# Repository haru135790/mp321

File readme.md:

# mp321-mpみつい

## 概要
mp321は、コンパクトな左手デバイスです。名刺サイズの基板に６つのキーとロータリーエンコーダーが搭載されています。
vialを使用してキー割り当てを自由に変更できます。

## 準備物
- mp321本体
- USBケーブル(AtoCまたはCtoC)
注意点：USBケーブルは通信ができるものを使用してください。100均等で「充電専用」として販売されているものは使用出来ません。

## キー割り当ての変更
本機のキー割り当ては「[vial](https://get.vial.today)」というソフトウェアを使用することで変更できます。
vialにはwebブラウザ版とアプリケーション版があり、ブラウザ版はChrome、アプリ版はWindows,macOS,Linuxで動作します。
また、2025/10/21時点で、vialは日本語対応していません。ご注意ください。

ここでは、vialを使用するとできることについて簡単に説明します。(詳細な操作方法等についてはネットで検索するか、後述の参考記事をご覧ください)
1. キーマップの変更
   - キーに割り当てられた機能を自由に変更できます。
   - キーボードに実際にあるキーだけでなく、メディアキー(音楽の再生/停止など)や、特殊キー(画面の明るさ調整など)も割り当て可能です。
   - 複数のキーを同時に押すショートカット(例: Ctrl+C)も一つのキーに割り当てられます。
2. マクロの設定
   - 複数のキー操作を一つのキーにまとめて割り当てることができます。
   - 例えば、「Ctrl+Aで全選択したあとに、Ctrl+Cでコピーする」といった連続した動作を一つのキーに設定することが可能です。
   - テキストの入力(「Hello, World!」と入力するなど)もマクロに含めることができます。
3. レイヤー機能
   - 複数のキーマップを作成し、特定のキーを押すことでキーマップを切り替えることができます。
   - 例えば、通常のキーマップと、ゲーム用のキーマップを切り替えることが可能です。
4. コンボキー
   - 複数のキーを同時に押すことで、別の機能を発動させることができます。
   - 例えば、AキーとBキーを同時に押すとCキーの機能が発動するように設定できます。
5. タップダンス
   - キーの押し方(単押し、長押し、単押し2回、単押しした直後に長押し)によって、異なる機能を割り当てることができます。
   - 例えば、普通にAキーを押すとAキーの機能が発動し、長押しするとBキーの機能が発動するように設定できます。

## 参考記事
vialの詳細な使用方法については、こちらの記事がおすすめです。
- [【初心者向け】Vialでキーボードをカスタムしよう！](https://alektor.hatenablog.com/entry/2024/11/15/233435)
- [（初心者編）Vialを使ってキーマップを書き換えよう-自作キーボード温泉街の歩き方](https://salicylic-acid3.hatenablog.com/entry/vial-manual)

## デフォルトキーマップ
mp321は初期状態では次のようなキー設定となっています。

mp321についているノブ(ロータリーエンコーダー)は、vial上では右回転と左回転、押し込みがそれぞれ分かれて表示されています。

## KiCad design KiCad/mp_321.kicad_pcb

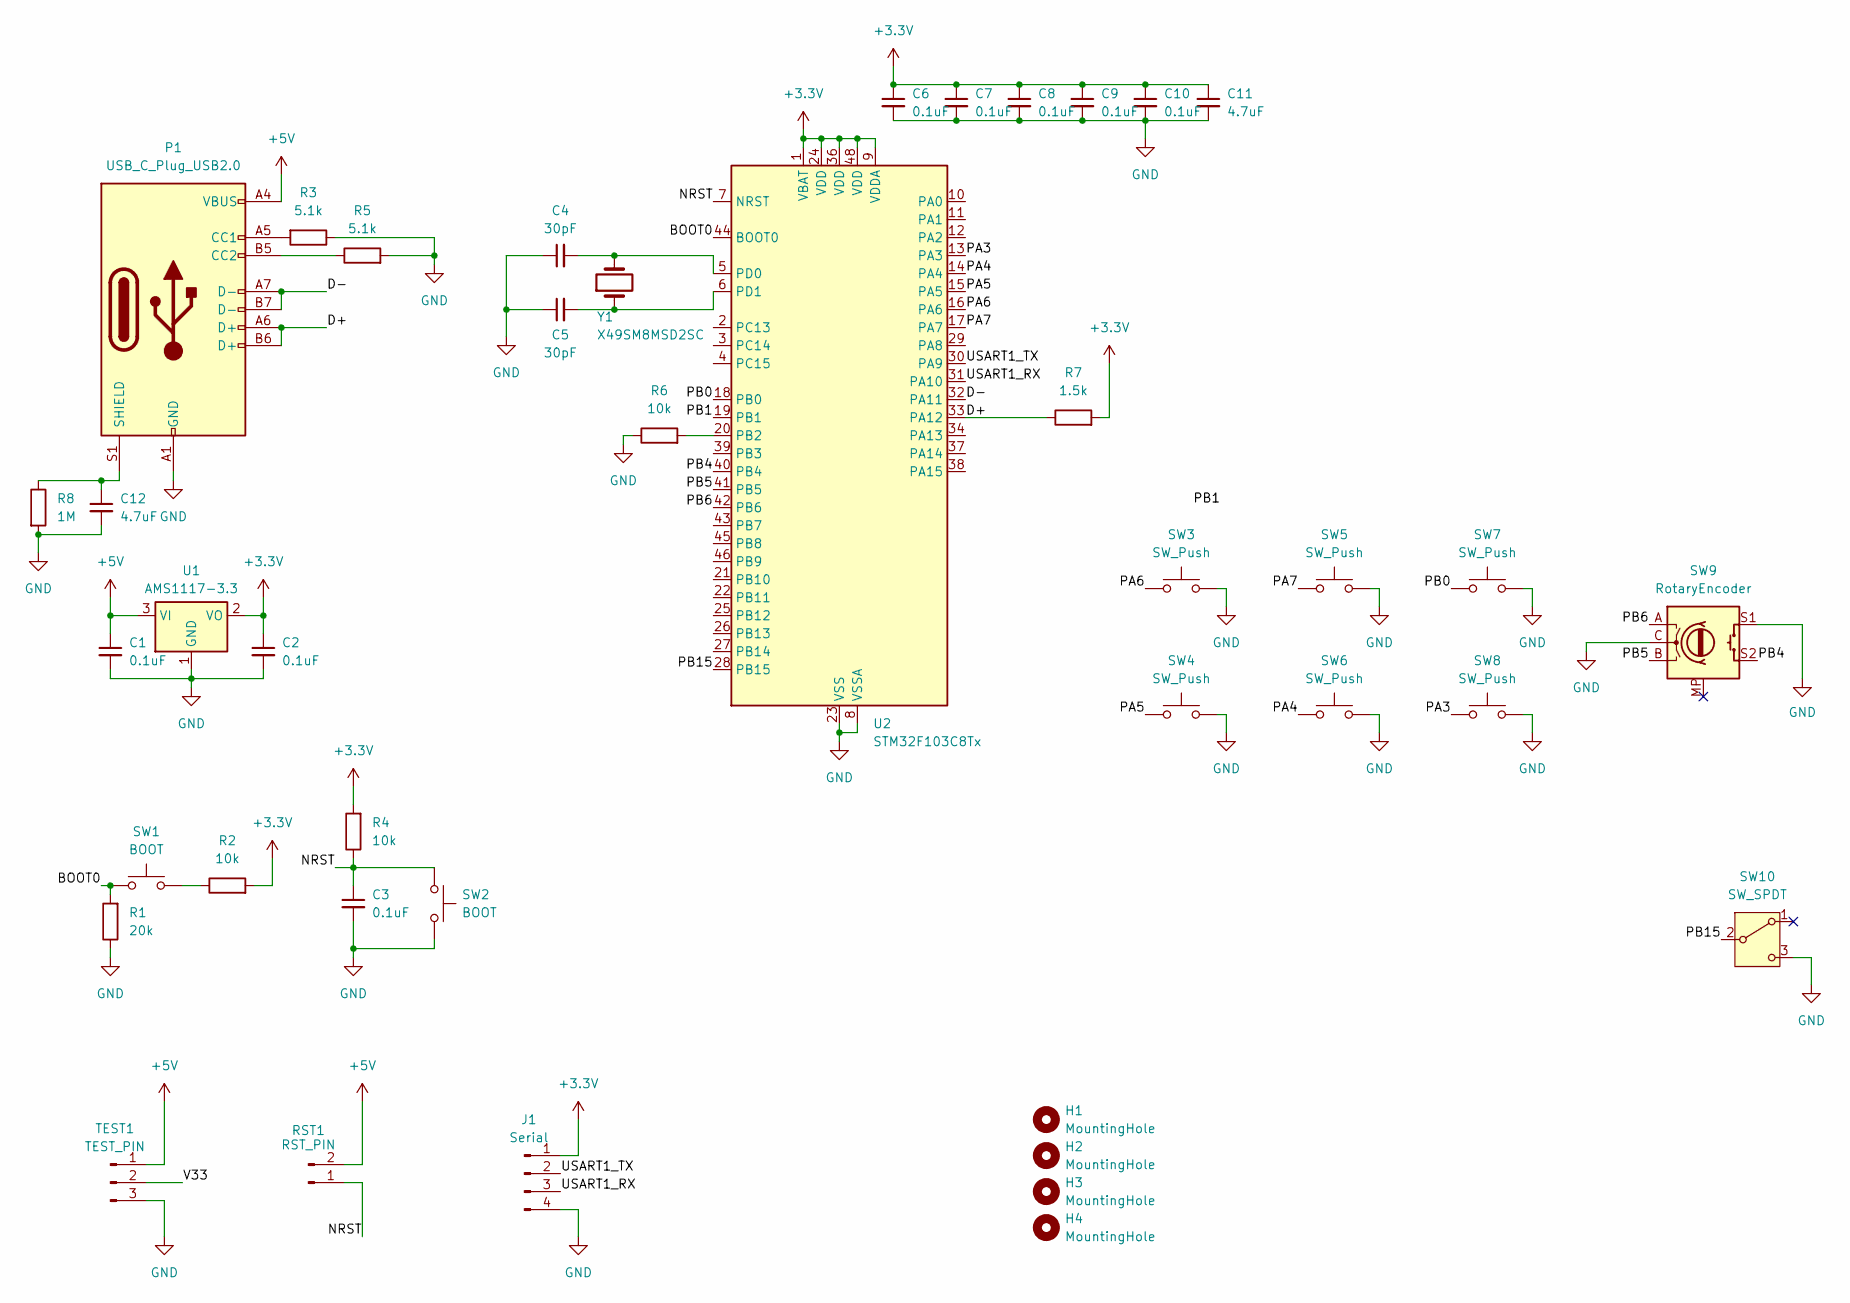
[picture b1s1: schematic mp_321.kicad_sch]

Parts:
C1, C2, C3, C6, C7, C8, C9, C10: 0.1uF; C_0603_1608Metric
C4, C5: 30pF; C_0603_1608Metric
C11, C12: 4.7uF; C_0603_1608Metric
H1, H2, H3, H4: MountingHole; MountingHole_3.2mm_M3
J1: Serial; PinHeader_1x04_P2.54mm_Vertical
P1: USB_C_Plug_USB2.0; USB_C_Receptacle_GCT_USB4105-xx-A_16P_TopMnt_Horizontal
R1: 20k; R_0603_1608Metric
R2, R4, R6: 10k; R_0603_1608Metric
R3, R5: 5.1k; R_0603_1608Metric
R7: 1.5k; R_0603_1608Metric
R8: 1M; R_0603_1608Metric
RST1: RST_PIN; TestPoint_2Pads_Pitch2.54mm_Drill0.8mm
SW1, SW2: BOOT; SW_Push_1P1T_XKB_TS-1187A
SW3, SW4, SW5, SW6, SW7, SW8: SW_Push; SW_Cherry_MX_PCB_1.00u
SW9: RotaryEncoder; RotaryEncoder_Alps_EC11E-Switch_Vertical_H20mm
SW10: SW_SPDT; SW_Push_1P1T-MP_NO_Horizontal_Alps_SSAJ120100
TEST1: TEST_PIN; PinSocket_1x03_P2.54mm_Vertical
U1: AMS1117-3.3; SOT-223-3_TabPin2
U2: STM32F103C8Tx; LQFP-48_7x7mm_P0.5mm
Y1: X49SM8MSD2SC; Crystal_SMD_HC49-SD

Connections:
+3.3V: C2.1, C6.1, C7.1, C8.1, C9.1, C10.1, C11.1, J1.1, R2.2, R4.2, R7.2, U1.2 (VO), U2.1 (VBAT), U2.9 (VDDA), U2.24 (VDD), U2.36 (VDD), U2.48 (VDD)
+5V: C1.1, P1.A4 (VBUS), P1.A9 (VBUS), P1.B4 (VBUS), P1.B9 (VBUS), RST1.2, TEST1.1, U1.3 (VI)
/BOOT0: R1.2, SW1.1, U2.44 (BOOT0)
/D+: P1.A6 (D+), P1.B6 (D+), R7.1, U2.33 (PA12)
/D-: P1.A7 (D-), P1.B7 (D-), U2.32 (PA11)
/NRST: C3.1, R4.1, RST1.1, SW2.1, U2.7 (NRST)
/PA3: SW8.1, U2.13 (PA3)
/PA4: SW6.1, U2.14 (PA4)
/PA5: SW4.1, U2.15 (PA5)
/PA6: SW3.1, U2.16 (PA6)
/PA7: SW5.1, U2.17 (PA7)
/PB0: SW7.1, U2.18 (PB0)
/PB1: U2.19 (PB1)
/PB4: SW9.S2, U2.40 (PB4)
/PB5: SW9.B, U2.41 (PB5)
/PB6: SW9.A, U2.42 (PB6)
/PB15: SW10.2 (B), U2.28 (PB15)
/USART1_RX: J1.3, U2.31 (PA10)
/USART1_TX: J1.2, U2.30 (PA9)
GND: C1.2, C2.2, C3.2, C4.1, C5.1, C6.2, C7.2, C8.2, C9.2, C10.2, C11.2, C12.2, J1.4, P1.A1 (GND), P1.A12 (GND), P1.B1 (GND), P1.B12 (GND), R1.1, R3.1, R5.2, R6.1, R8.2, SW2.2, SW3.2, SW4.2, SW5.2, SW6.2, SW7.2, SW8.2, SW9.C, SW9.S1, SW10.3 (C), TEST1.3, U1.1 (GND), U2.8 (VSSA), U2.23 (VSS), U2.35 (VSS), U2.47 (VSS)
unnamed: P1.A5 (CC1), R3.2
unnamed: P1.B5 (CC2), R5.1
unnamed: C12.1, P1.S1 (SHIELD), R8.1
unnamed: R2.1, SW1.2
unnamed: R6.2, U2.20 (PB2)
unnamed: C4.2, U2.5 (PD0), Y1.2
unnamed: C5.2, U2.6 (PD1), Y1.1

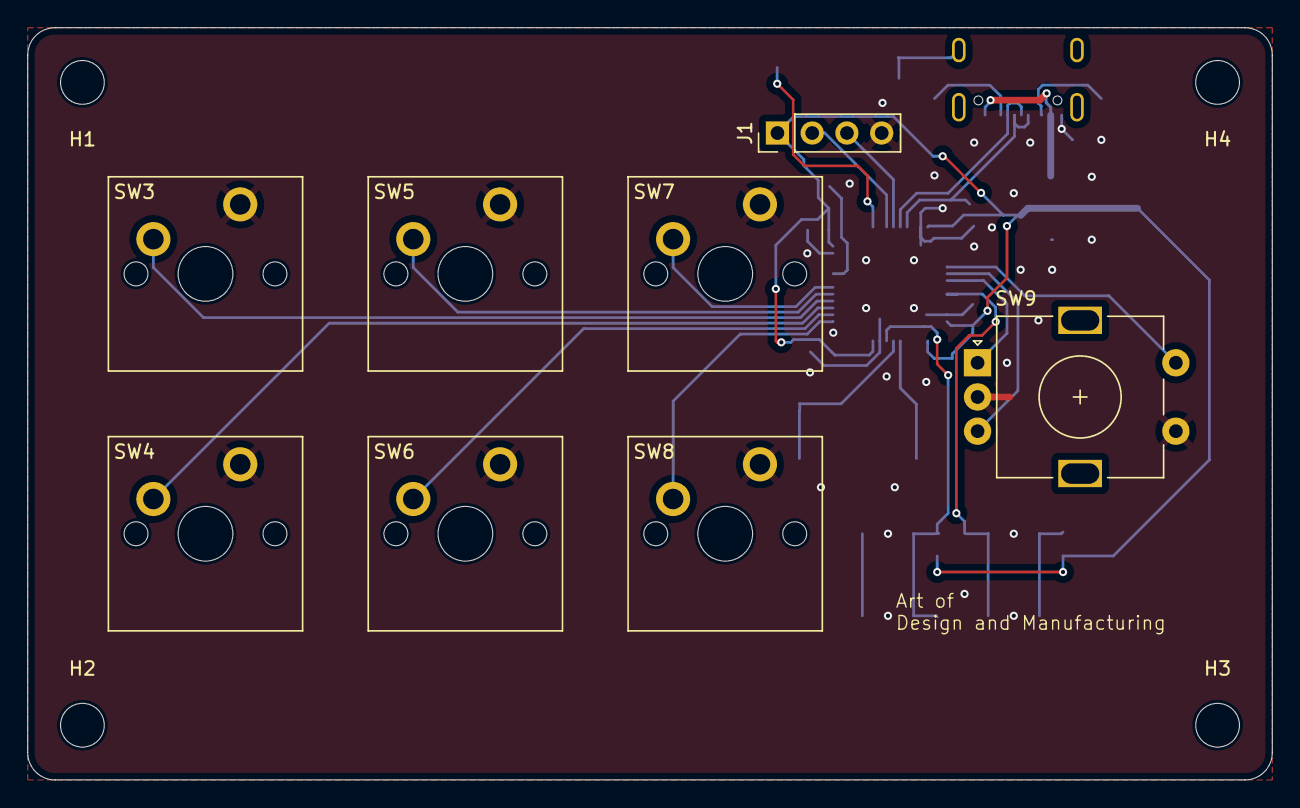
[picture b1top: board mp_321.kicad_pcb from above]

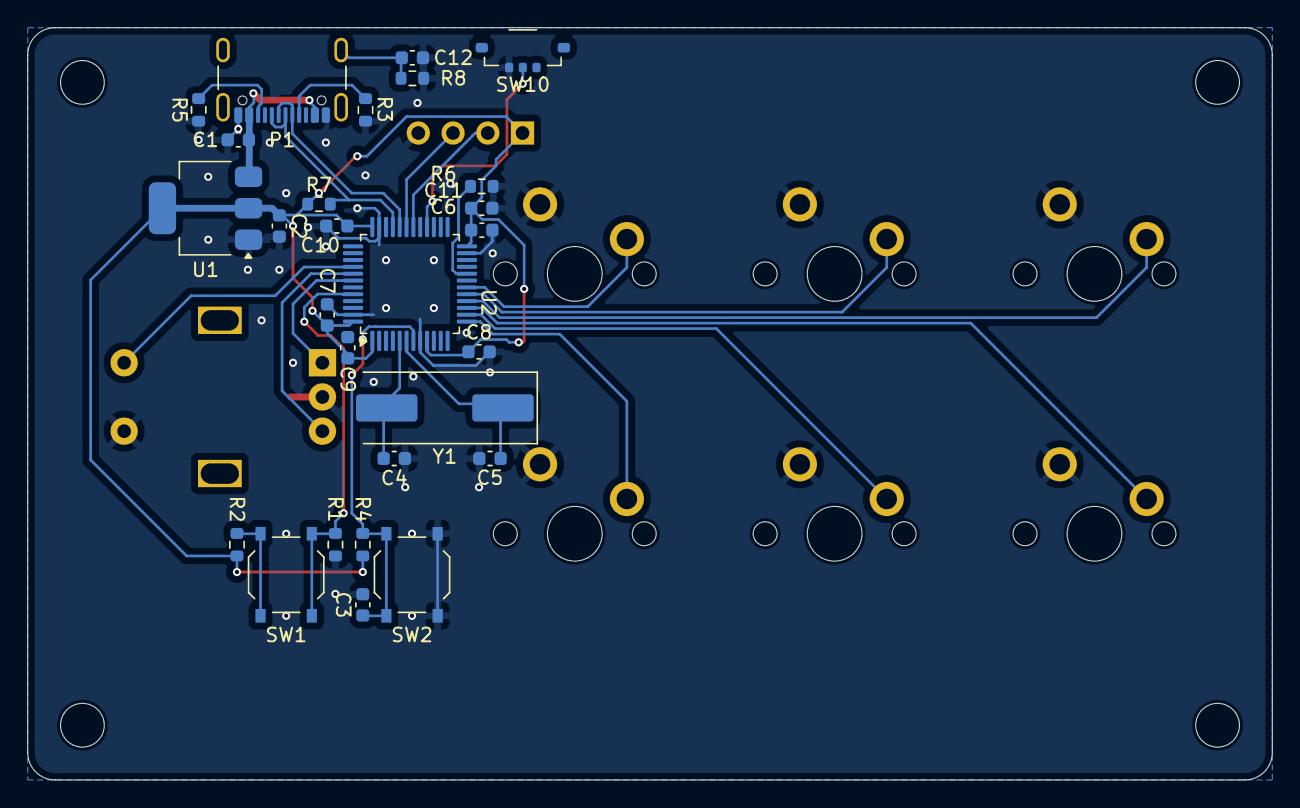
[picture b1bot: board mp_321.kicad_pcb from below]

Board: 2 copper layers, 91.0 x 55.0 mm, 39 parts (27 on the bottom side), 26 nets.

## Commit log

2025-10-24 デフォルトキーマップの画像を追加
2025-10-24 ディレクトリ構造を整理
2025-10-25 readme.mdのリンク切れを修正
2025-10-25 readme.md を更新
